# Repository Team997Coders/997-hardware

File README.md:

# 997-Hardware
Repository for FRC 997's custom PCB projects, made in KiCad.

Documentation for each project can be found in their individual directories.

[KiCanvas](https://kicanvas.org/) is recommended for viewing projects from the browser. [Kiri](https://github.com/leoheck/kiri) is a very good tool for visual git diffs of KiCad files, but only runs locally and has quite a few dependencies.

### Installation
This project uses `kicad-cli` and `pcbdraw` in its commit hook script. `kicad-cli` is distributed with the broader KiCad package, and `pcbdraw` can be installed using [these instructions](https://github.com/yaqwsx/PcbDraw/blob/master/doc/installation.md).[^1]

### Licensing
Hardware source files licensed under the GPL v3.0. Some redistributed files may be under different licenses.

[^1]: `pcbdraw` depends on the `mistune` library. `pcbdraw` version 1.1.2 does not depend on the correct version of `mistune` and for some users manually running `pip install mistune==2.0.5` may be required.

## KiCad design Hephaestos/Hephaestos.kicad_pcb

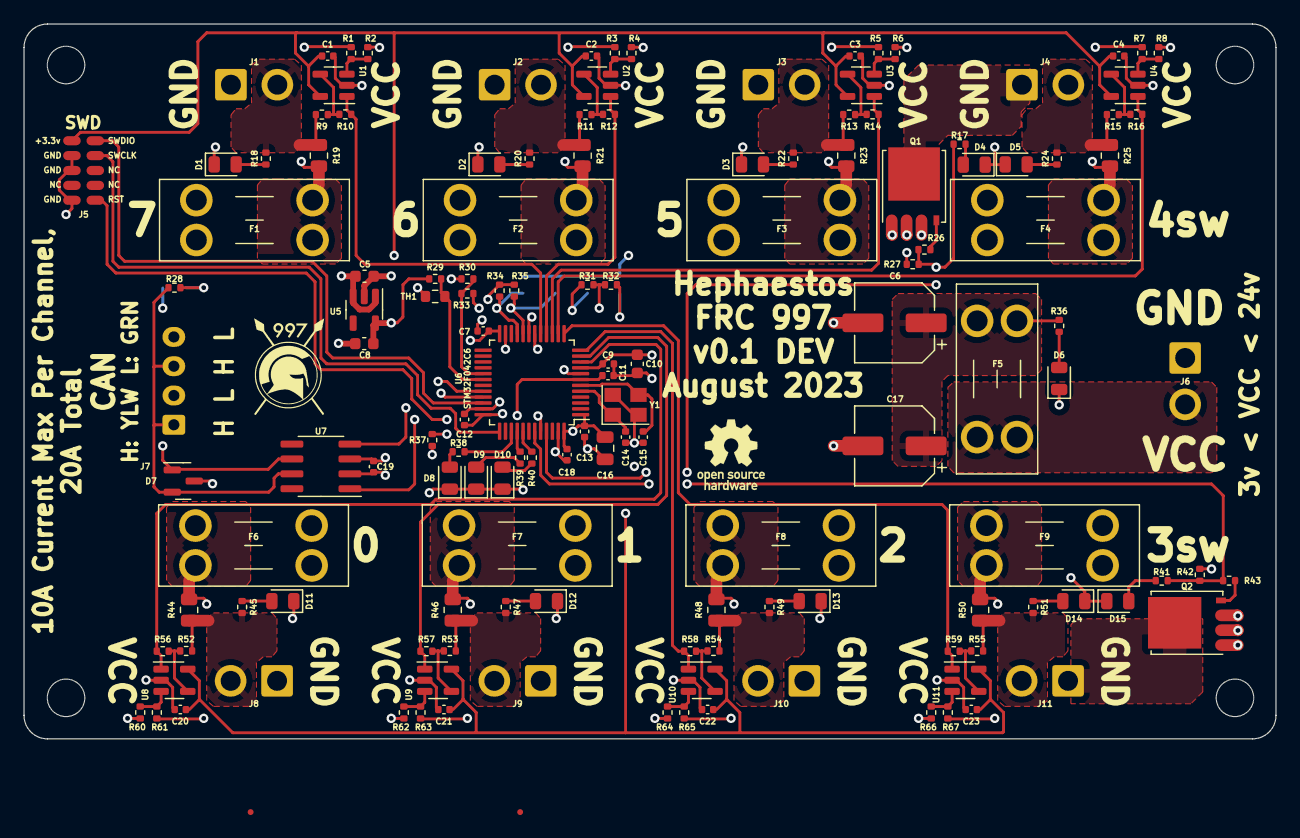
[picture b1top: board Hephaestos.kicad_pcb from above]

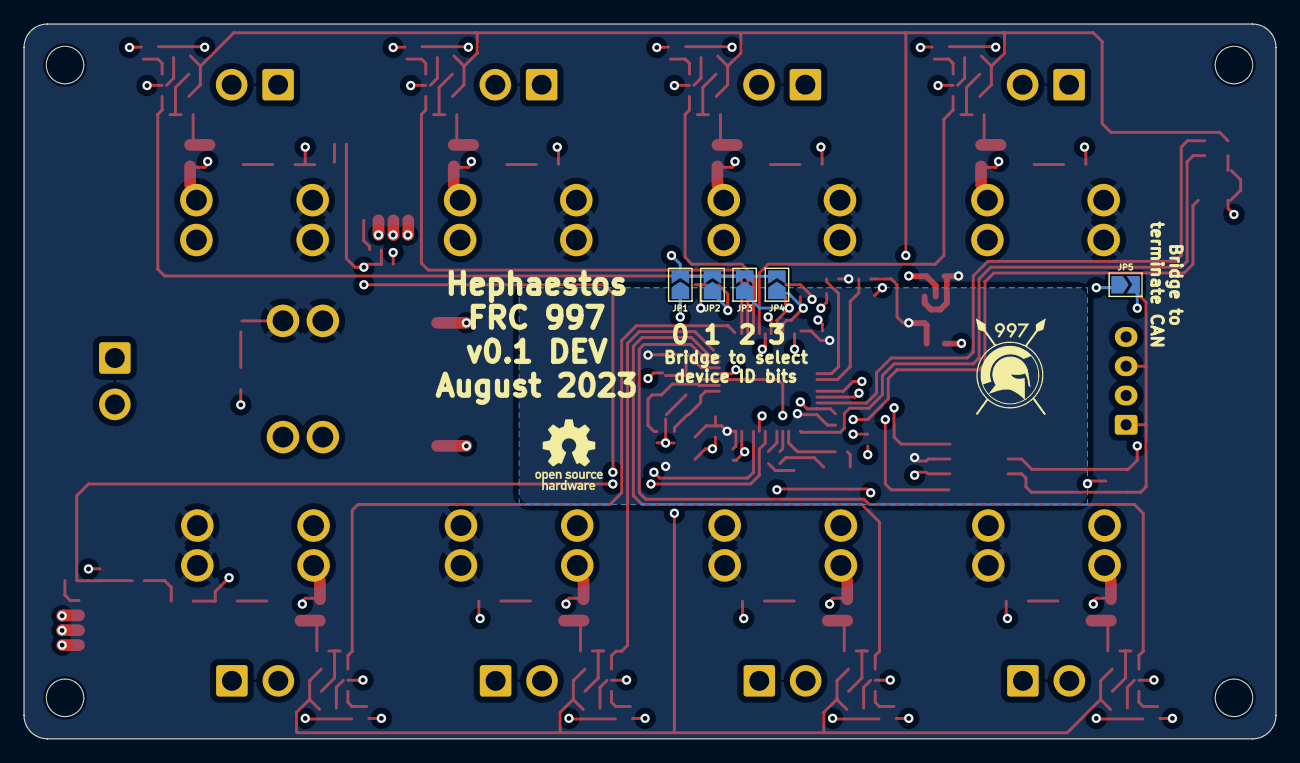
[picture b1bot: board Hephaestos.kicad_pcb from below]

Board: 4 copper layers, 106.8 x 61.0 mm, 149 parts (7 on the bottom side), 84 nets.

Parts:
1, 2: LOGO; 997-big
C1, C2, C3, C4, C7, C9, C11, C12, C13, C18, C19, C20, C21, C22, C23: 0.1 uF; C_0402_1005Metric
C5: 1 uF 35v; C_0603_1608Metric
C6, C17: 100 uF 35v; CP_Elec_6.3x7.7
C8: 2.2 uF; C_0603_1608Metric
C10: 1 uF; C_0603_1608Metric
C14, C15: 10 pF; C_0402_1005Metric
C16: 4.7 uF; C_0805_2012Metric
D1, D2, D3, D5, D6, D8, D11, D12, D13, D14: BLUE; LED_0805_2012Metric
D4, D10, D15: RED; LED_0805_2012Metric
D7: NUP2105L; SOT-23
D9: GREEN; LED_0805_2012Metric
F1, F2, F3, F4, F5, F6, F7, F8, F9: FUSE; Fuseholder_Blade_Mini_Keystone_3568
J1, J2, J3, J4, J6, J8, J9, J10, J11: Conn_01x02; JST_VH_B2P-VH-B_1x02_P3.96mm_Vertical
J5: Conn_02x05_Counter_Clockwise; Tag-Connect_TC2050-IDC-FP_2x05_P1.27mm_Vertical
J7: Conn_01x04; JST_XH_B4B-XH-AM_1x04_P2.50mm_Vertical
JP1, JP2, JP3, JP4, JP5: Jumper_2_Open; SolderJumper-2_P1.3mm_Open_TrianglePad1.0x1.5mm
Q1, Q2: CSD17577Q5A; TDSON-8-1
R1, R3, R5, R7, R9, R11, R13, R15, R17, R41, R52, R53, R54, R55, R61, R63, R65, R67: 200; R_0402_1005Metric
R2, R4, R6, R8, R10, R12, R14, R16, R56, R57, R58, R59, R60, R62, R64, R66: 15k; R_0402_1005Metric
R18, R20, R22, R24, R26, R27, R29, R30, R31, R32, R34, R35, R36, R37, R42, R43, R45, R47, R49, R51: 1k; R_0402_1005Metric
R19, R21, R23, R25, R44, R46, R48, R50: 0.003; R_0805_2012Metric
R28: 120; R_0402_1005Metric
R33, R40: 100; R_0402_1005Metric
R38, R39: 22; R_0402_1005Metric
TH1: thermistor 10k; R_0603_1608Metric
U1, U2, U3, U4, U8, U9, U10, U11: MCP6001-OT; SOT-23-5
U5: AP2205K-3.3; SOT-23-5
U6: STM32F042C6Tx; LQFP-48_7x7mm_P0.5mm
U7: SN65HVD232; SOIC-8_3.9x4.9mm_P1.27mm
Y1: 16 MHz 9 pF; Crystal_SMD_3225-4Pin_3.2x2.5mm
oshw_b: OSHW-Logo_5.7x6mm_SilkScreen
oshw_f: OSHW-Logo_5.7x6mm_SilkScreen

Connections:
+3.3V: C1.1, C2.1, C3.1, C4.1, C7.2, C8.2, C9.2, C10.1, C12.2, C13.2, C16.2, C18.2, C19.2, C20.1, C21.1, C22.1, C23.1, J5.1, R29.1, R31.1, R32.1, R34.1, R35.1, U1.5 (V+), U2.5 (V+), U3.5 (V+), U4.5 (V+), U5.5 (VOUT), U6.1 (VBAT), U6.9 (VDDA), U6.24 (VDD), U6.36 (VDDIO2), U6.48 (VDD), U7.3 (VCC), U8.5 (V+), U9.5 (V+), U10.5 (V+), U11.5 (V+)
/channel0/L: J8.2, R44.1, R45.2, R52.2
/channel1/L: J9.2, R46.1, R47.2, R53.2
/channel2/L: J10.2, R48.1, R49.2, R54.2
/channel3/L: J11.2, R50.1, R51.2, R55.2
/channel4/L: J4.2, R15.2, R24.2, R25.1
/channel5/L: J3.2, R13.2, R22.2, R23.1
/channel6/L: J2.2, R11.2, R20.2, R21.1
/channel7/L: J1.2, R9.2, R18.2, R19.1
A0: R56.2, U6.10 (PA0), U8.1
A1: R57.2, U6.11 (PA1), U9.1
A2: R58.2, U6.12 (PA2), U10.1
A3: R59.2, U6.13 (PA3), U11.1
A4: R16.2, U4.1, U6.14 (PA4)
A5: R14.2, U3.1, U6.15 (PA5)
A6: R12.2, U2.1, U6.16 (PA6)
A7: R10.2, U1.1, U6.17 (PA7)
ADC_THERM: R29.2, TH1.1, U6.30 (PA9)
ADC_VCCDIV: R30.2, R33.1, U6.29 (PA8)
CANH: D7.2 (K), J7.1, J7.3, R28.1, U7.7 (CANH)
CANID_SEL_0: JP1.1 (A), R32.2, U6.18 (PB0)
CANID_SEL_1: JP2.1 (A), R31.2, U6.19 (PB1)
CANID_SEL_2: JP3.1 (A), R35.2, U6.20 (PB2)
CANID_SEL_3: JP4.1 (A), R34.2, U6.21 (PB10)
CANL: D7.1 (K), J7.2, J7.4, JP5.2 (B), U7.6 (CANL)
CAN_RX: U6.32 (PA11), U7.4 (R)
CAN_TX: U6.33 (PA12), U7.1 (D)
CLK_A: C14.2, U6.5 (PF0), Y1.1
CLK_B: C15.1, U6.6 (PF1), Y1.3
GND: C1.2, C2.2, C3.2, C4.2, C5.2, C6.2, C7.1, C8.1, C9.1, C10.2, C11.1, C12.1, C13.1, C14.1, C15.2, C16.1, C17.2, C18.1, C19.1, C20.2, C21.2, C22.2, C23.2, D1.1 (K), D2.1 (K), D3.1 (K), D4.1 (K), D5.1 (K), D6.1 (K), D7.3 (A), D8.1 (K), D9.1 (K), D10.1 (K), D11.1 (K), D12.1 (K), D13.1 (K), D14.1 (K), D15.1 (K), J1.1, J2.1, J3.1, J5.2, J5.3, J5.5, J6.1, J8.1, J9.1, J10.1, JP1.2 (B), JP2.2 (B), JP3.2 (B), JP4.2 (B), Q1.1 (S), Q1.2 (S), Q1.3 (S), Q2.1 (S), Q2.2 (S), Q2.3 (S), R2.2, R4.2, R6.2, R8.2, R27.2, R33.2, R37.2, R42.2, R60.2, R62.2, R64.2, R66.2, TH1.2, U1.2 (V-), U2.2 (V-), U3.2 (V-), U4.2 (V-), U5.2 (GND), U6.8 (VSSA), U6.23 (VSS), U6.35 (VSS), U6.47 (VSS), U7.2 (GND), U8.2 (V-), U9.2 (V-), U10.2 (V-), U11.2 (V-), Y1.2, Y1.4
LED_B: R38.1, U6.39 (PB3)
LED_G: R39.1, U6.40 (PB4)
LED_R: R40.1, U6.41 (PB5)
unnamed: D1.2 (A), R18.1
unnamed: D2.2 (A), R20.1
unnamed: D3.2 (A), R22.1
unnamed: D4.2 (A), R17.1
unnamed: D5.2 (A), R24.1
unnamed: D6.2 (A), R36.1
unnamed: D8.2 (A), R38.2
unnamed: D9.2 (A), R39.2
unnamed: D10.2 (A), R40.2
unnamed: D11.2 (A), R45.1
unnamed: D12.2 (A), R47.1
unnamed: D13.2 (A), R49.1
unnamed: D14.2 (A), R51.1
unnamed: D15.2 (A), R41.1
unnamed: F1.1, R1.2, R19.2
unnamed: F2.1, R3.2, R21.2
unnamed: F3.1, R5.2, R23.2
unnamed: F4.1, R7.2, R25.2
unnamed: F6.1, R44.2, R61.2
unnamed: F7.1, R46.2, R63.2
unnamed: F8.1, R48.2, R65.2
unnamed: F9.1, R50.2, R67.2
unnamed: J4.1, Q1.5 (D)
unnamed: F5.1, J6.2
unnamed: J11.1, Q2.5 (D)
unnamed: JP5.1 (A), R28.2
unnamed: Q1.4 (G), R26.2
unnamed: Q2.4 (G), R43.2
unnamed: R1.1, R2.1, U1.3 (+)
unnamed: R9.1, R10.1, U1.4 (-)
unnamed: R3.1, R4.1, U2.3 (+)
unnamed: R11.1, R12.1, U2.4 (-)
unnamed: R5.1, R6.1, U3.3 (+)
unnamed: R13.1, R14.1, U3.4 (-)
unnamed: R7.1, R8.1, U4.3 (+)
unnamed: R15.1, R16.1, U4.4 (-)
unnamed: R60.1, R61.1, U8.3 (+)
unnamed: R52.1, R56.1, U8.4 (-)
unnamed: R62.1, R63.1, U9.3 (+)
unnamed: R53.1, R57.1, U9.4 (-)
unnamed: R64.1, R65.1, U10.3 (+)
unnamed: R54.1, R58.1, U10.4 (-)
unnamed: R66.1, R67.1, U11.3 (+)
unnamed: R55.1, R59.1, U11.4 (-)
unnamed: R37.1, U6.44 (PF11)
RST: C11.2, J5.6, U6.7 (NRST)
SW3: R41.2, R42.1, R43.1, U6.43 (PB7)
SW4: R17.2, R26.1, R27.1, U6.45 (PB8)
SWCLK: J5.9, U6.37 (PA14)
SWDIO: J5.10, U6.34 (PA13)
VCC: C5.1, C6.1, C17.1, F1.2, F2.2, F3.2, F4.2, F5.2, F6.2, F7.2, F8.2, F9.2, R30.1, R36.2, U5.1 (VIN), U5.3 (EN)

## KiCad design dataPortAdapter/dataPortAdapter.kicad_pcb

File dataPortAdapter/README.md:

# Data Port Adapter

<center> </center>

A simple, completely passive board to convert between the slightly different pinouts of the SparkMAX and the SRX Mag Encoder, intended as a way to get a simpler and cheaper absolute encoder option mechanically compatible with the de-facto standard CANCoder.

The STEP file REV-11-2158 (for 3d visualization) is redistributed from REV Robotics and subject to its original licensing.

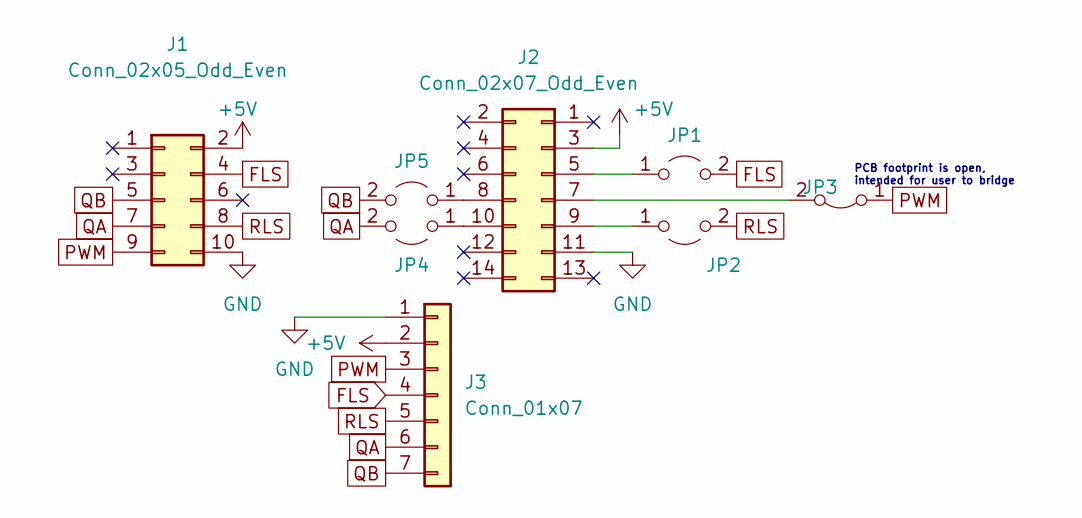
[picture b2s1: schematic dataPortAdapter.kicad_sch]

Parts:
J1: Conn_02x05_Odd_Even; PinHeader_2x05_P1.27mm_Vertical
J2: Conn_02x07_Odd_Even; PinHeader_2x07_P1.27mm_Vertical
J3: Conn_01x07; PinSocket_1x07_P2.54mm_Vertical
JP1, JP2, JP4, JP5: Jumper_2_Open; SolderJumper-2_P1.3mm_Open_TrianglePad1.0x1.5mm
JP3: Jumper_2_Bridged; SolderJumper-2_P1.3mm_Open_TrianglePad1.0x1.5mm

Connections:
+5V: J1.2, J2.3, J3.2
FLS: J1.4, J3.4, JP1.2 (B)
GND: J1.10, J2.11, J3.1
unnamed: J2.5, JP1.1 (A)
unnamed: J2.7, JP3.2 (B)
unnamed: J2.8, JP5.1 (A)
unnamed: J2.9, JP2.1 (A)
unnamed: J2.10, JP4.1 (A)
PWM: J1.9, J3.3, JP3.1 (A)
QA: J1.7, J3.6, JP4.2 (B)
QB: J1.5, J3.7, JP5.2 (B)
RLS: J1.8, J3.5, JP2.2 (B)

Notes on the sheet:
PCB footprint is open, intended for user to bridge

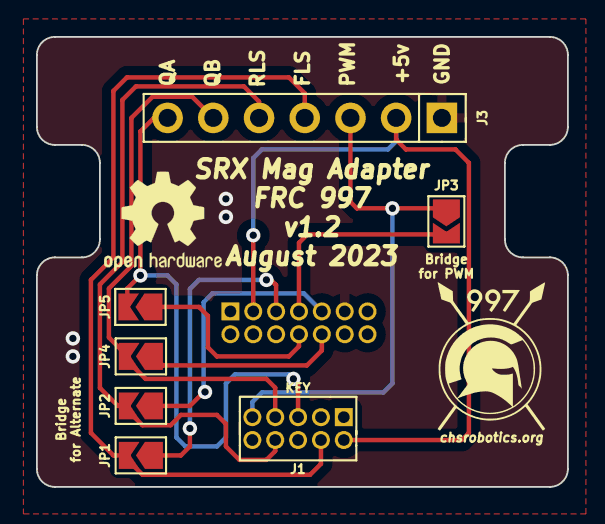
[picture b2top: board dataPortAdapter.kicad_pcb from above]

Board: 2 copper layers, 29.5 x 25.0 mm, 8 parts (1 on the bottom side), 12 nets.

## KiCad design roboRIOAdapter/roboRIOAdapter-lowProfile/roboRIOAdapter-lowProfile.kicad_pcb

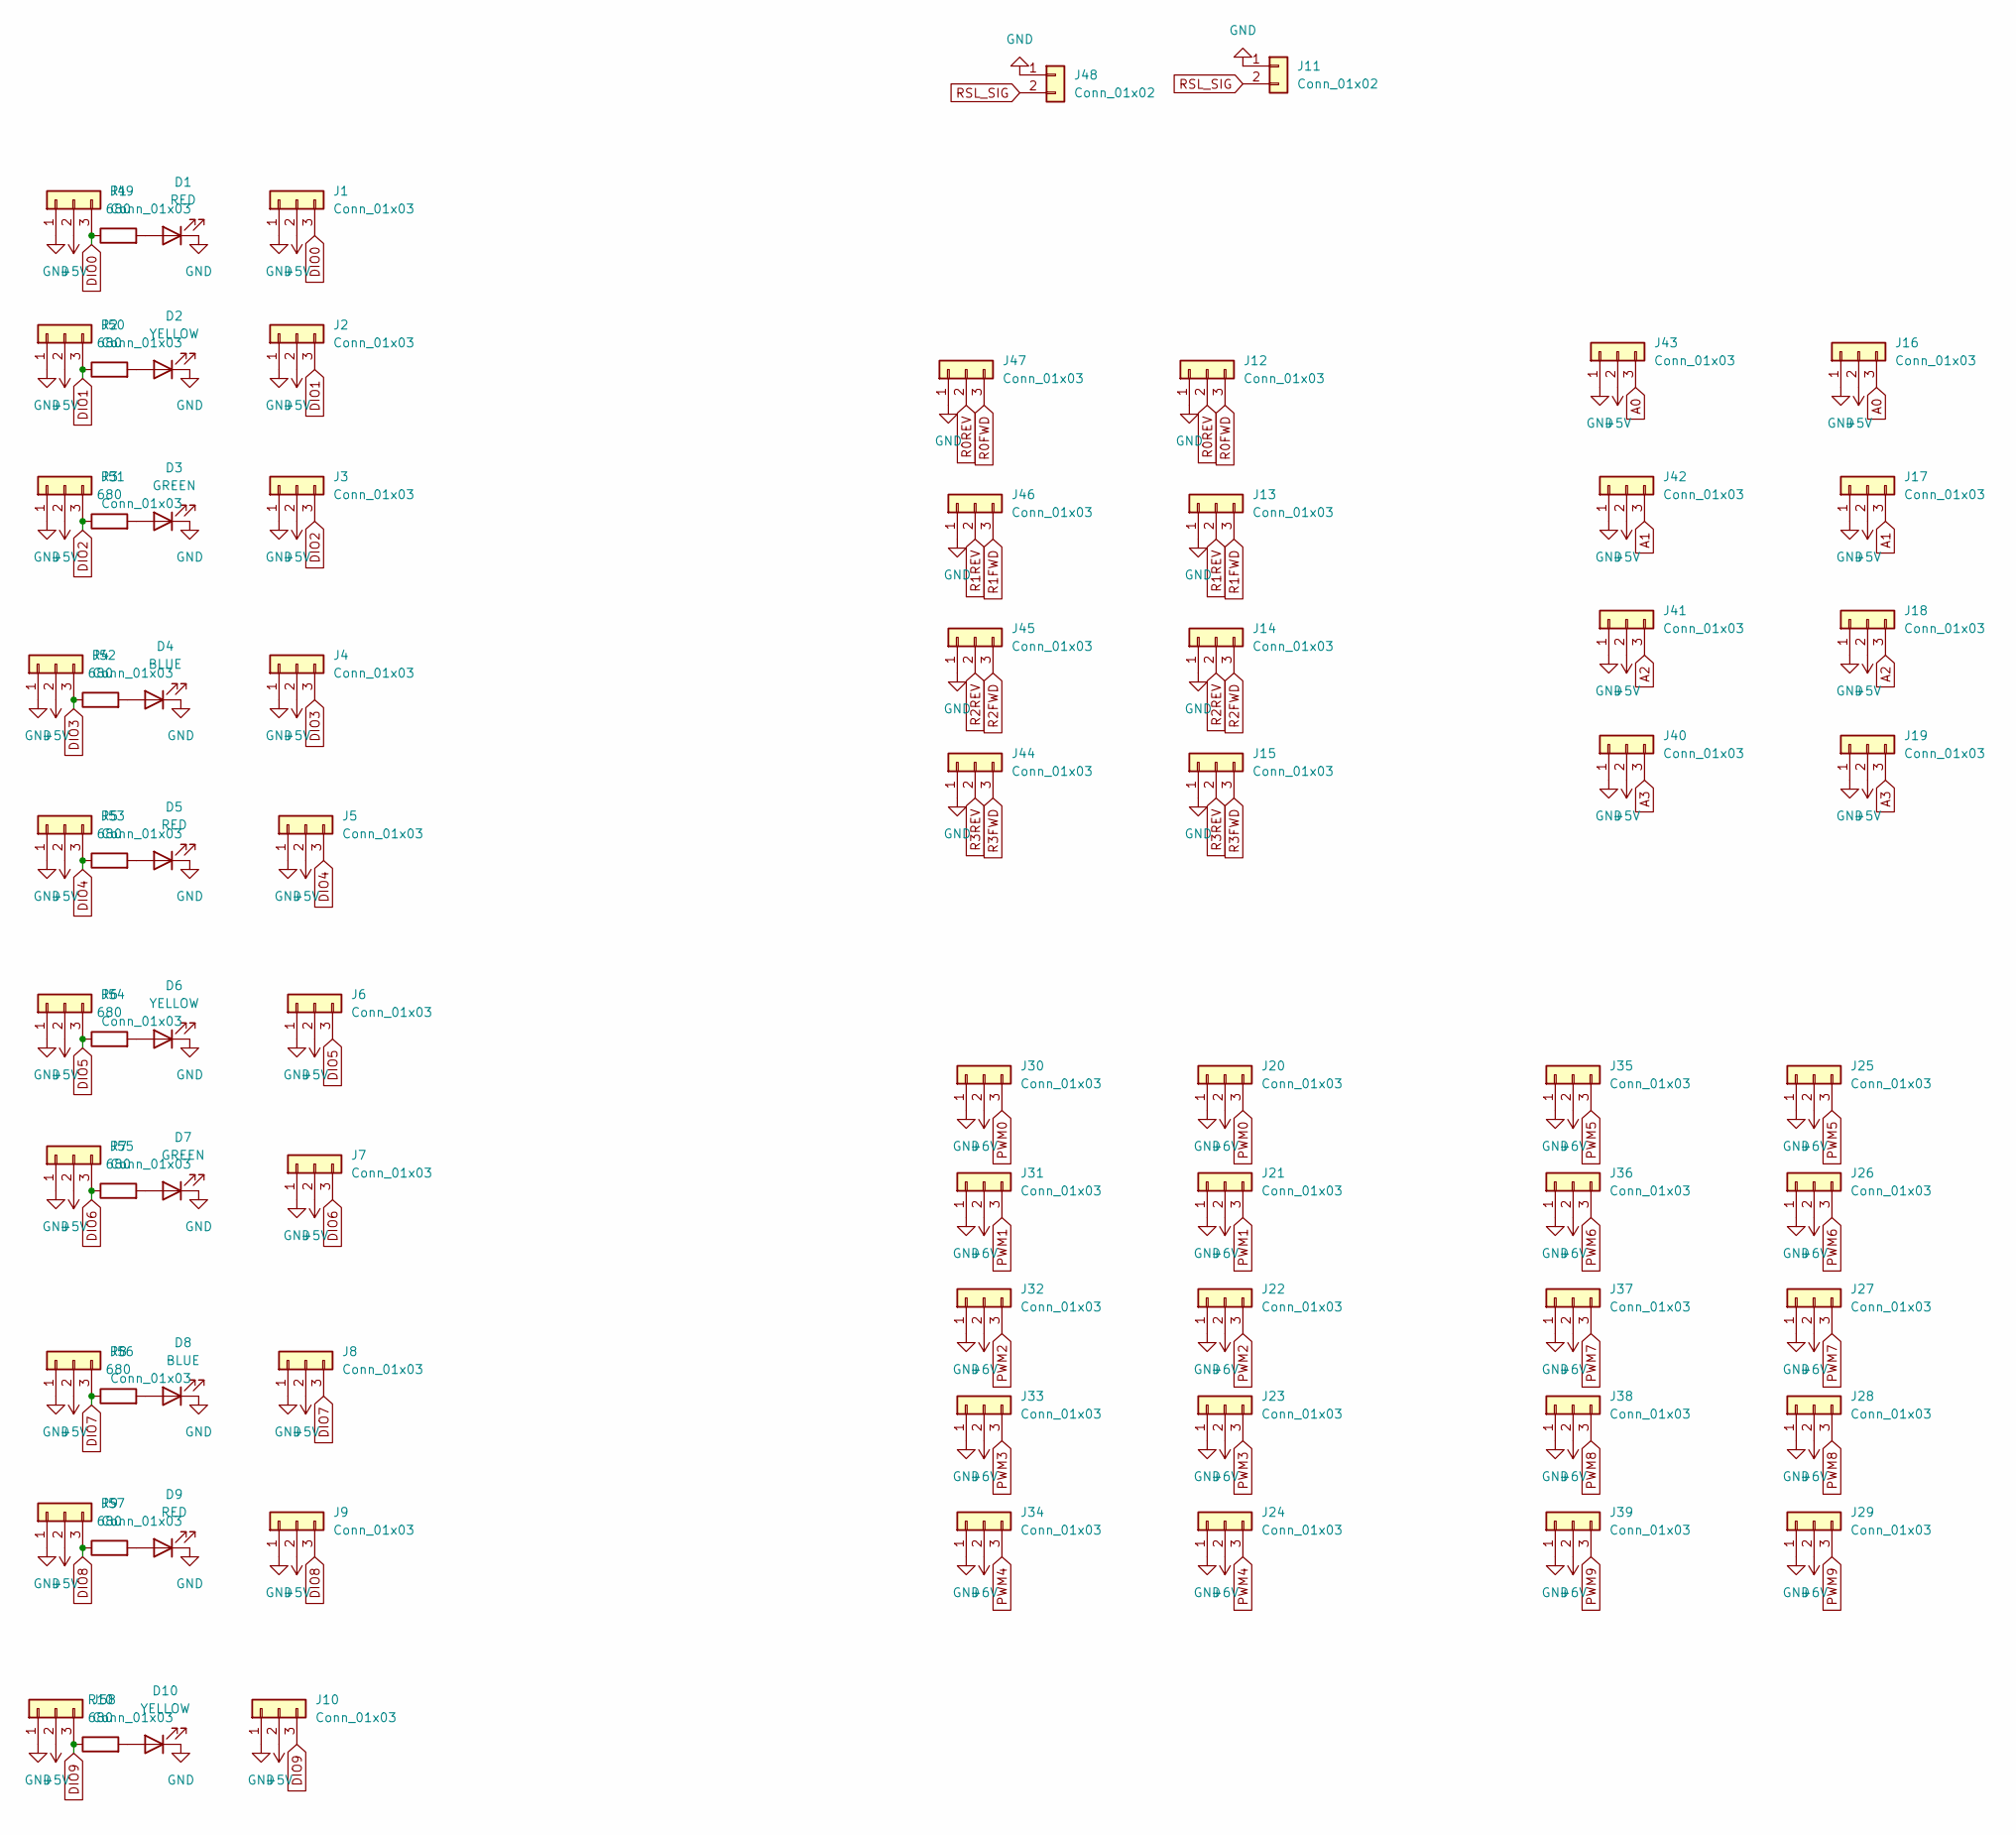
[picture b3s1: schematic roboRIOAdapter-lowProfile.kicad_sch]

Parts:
D1, D5, D9: RED; LED_0603_1608Metric
D2, D6, D10: YELLOW; LED_0603_1608Metric
D3, D7: GREEN; LED_0603_1608Metric
D4, D8: BLUE; LED_0603_1608Metric
J1, J2, J3, J4, J5, J6, J7, J8, J9, J10, J12, J13, J14, J15, J16, J17, J18, J19, J20, J21, J22, J23, J24, J25, J26, J27, J28, J29: Conn_01x03; JST_XH_B3B-XH-A_1x03_P2.50mm_Vertical
J11: Conn_01x02; JST_XH_B2B-XH-A_1x02_P2.50mm_Vertical
J30, J31, J32, J33, J34, J35, J36, J37, J38, J39, J40, J41, J42, J43, J44, J45, J46, J47, J49, J50, J51, J52, J53, J54, J55, J56, J57, J58: Conn_01x03; PinSocket_1x03_P2.54mm_Vertical
J48: Conn_01x02; PinSocket_1x02_P2.54mm_Vertical
R1, R2, R3, R4, R5, R6, R7, R8, R9, R10: 680; R_0603_1608Metric

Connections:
+5V: J1.2, J2.2, J3.2, J4.2, J5.2, J6.2, J7.2, J8.2, J9.2, J10.2, J16.2, J17.2, J18.2, J19.2, J40.2, J41.2, J42.2, J43.2, J49.2, J50.2, J51.2, J52.2, J53.2, J54.2, J55.2, J56.2, J57.2, J58.2
+6V: J20.2, J21.2, J22.2, J23.2, J24.2, J25.2, J26.2, J27.2, J28.2, J29.2, J30.2, J31.2, J32.2, J33.2, J34.2, J35.2, J36.2, J37.2, J38.2, J39.2
A0: J16.3, J43.3
A1: J17.3, J42.3
A2: J18.3, J41.3
A3: J19.3, J40.3
DIO0: J1.3, J49.3, R1.1
DIO1: J2.3, J50.3, R2.1
DIO2: J3.3, J51.3, R3.1
DIO3: J4.3, J52.3, R4.1
DIO4: J5.3, J53.3, R5.1
DIO5: J6.3, J54.3, R6.1
DIO6: J7.3, J55.3, R7.1
DIO7: J8.3, J56.3, R8.1
DIO8: J9.3, J57.3, R9.1
DIO9: J10.3, J58.3, R10.1
GND: D1.1 (K), D2.1 (K), D3.1 (K), D4.1 (K), D5.1 (K), D6.1 (K), D7.1 (K), D8.1 (K), D9.1 (K), D10.1 (K), J1.1, J2.1, J3.1, J4.1, J5.1, J6.1, J7.1, J8.1, J9.1, J10.1, J11.1, J12.1, J13.1, J14.1, J15.1, J16.1, J17.1, J18.1, J19.1, J20.1, J21.1, J22.1, J23.1, J24.1, J25.1, J26.1, J27.1, J28.1, J29.1, J30.1, J31.1, J32.1, J33.1, J34.1, J35.1, J36.1, J37.1, J38.1, J39.1, J40.1, J41.1, J42.1, J43.1, J44.1, J45.1, J46.1, J47.1, J48.1, J49.1, J50.1, J51.1, J52.1, J53.1, J54.1, J55.1, J56.1, J57.1, J58.1
unnamed: D1.2 (A), R1.2
unnamed: D2.2 (A), R2.2
unnamed: D3.2 (A), R3.2
unnamed: D4.2 (A), R4.2
unnamed: D5.2 (A), R5.2
unnamed: D6.2 (A), R6.2
unnamed: D7.2 (A), R7.2
unnamed: D8.2 (A), R8.2
unnamed: D9.2 (A), R9.2
unnamed: D10.2 (A), R10.2
PWM0: J20.3, J30.3
PWM1: J21.3, J31.3
PWM2: J22.3, J32.3
PWM3: J23.3, J33.3
PWM4: J24.3, J34.3
PWM5: J25.3, J35.3
PWM6: J26.3, J36.3
PWM7: J27.3, J37.3
PWM8: J28.3, J38.3
PWM9: J29.3, J39.3
R0FWD: J12.3, J47.3
R0REV: J12.2, J47.2
R1FWD: J13.3, J46.3
R1REV: J13.2, J46.2
R2FWD: J14.3, J45.3
R2REV: J14.2, J45.2
R3FWD: J15.3, J44.3
R3REV: J15.2, J44.2
RSL_SIG: J11.2, J48.2

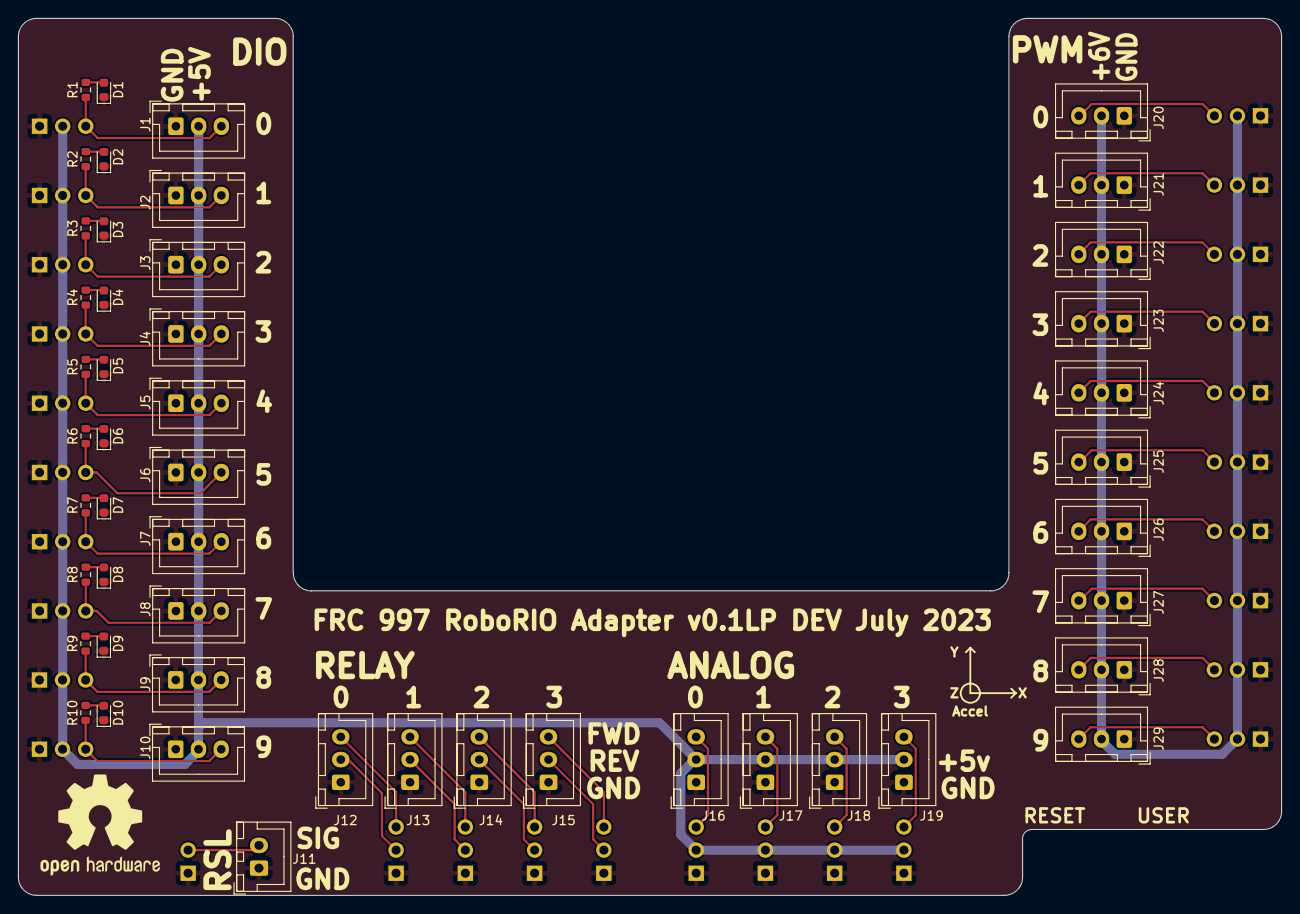
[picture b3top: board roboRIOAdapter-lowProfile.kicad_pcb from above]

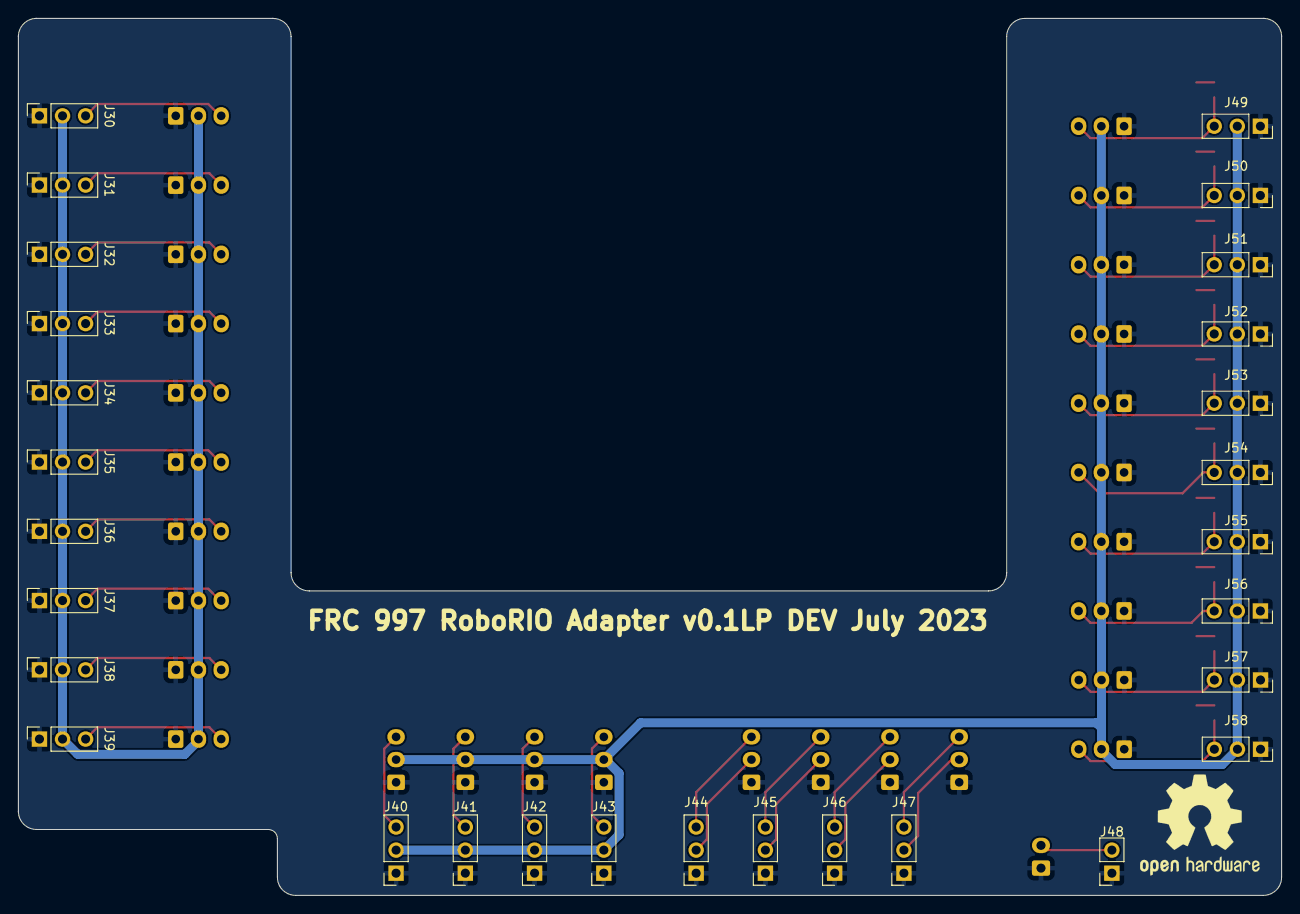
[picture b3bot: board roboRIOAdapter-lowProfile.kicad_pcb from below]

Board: 4 copper layers, 139.0 x 96.5 mm, 78 parts (29 on the bottom side), 46 nets.

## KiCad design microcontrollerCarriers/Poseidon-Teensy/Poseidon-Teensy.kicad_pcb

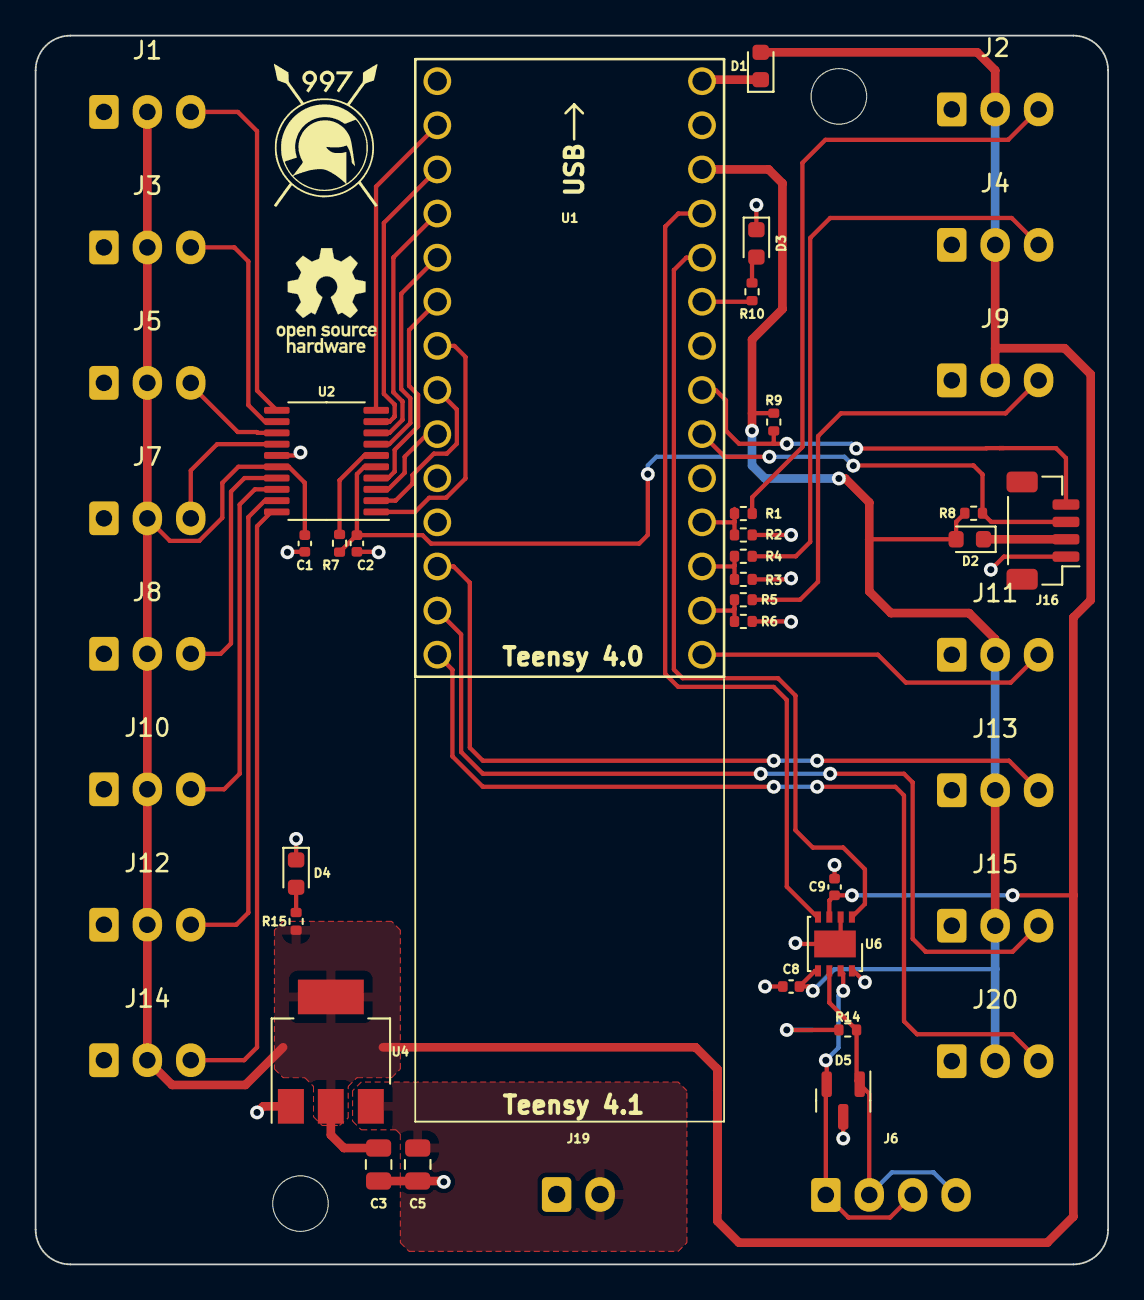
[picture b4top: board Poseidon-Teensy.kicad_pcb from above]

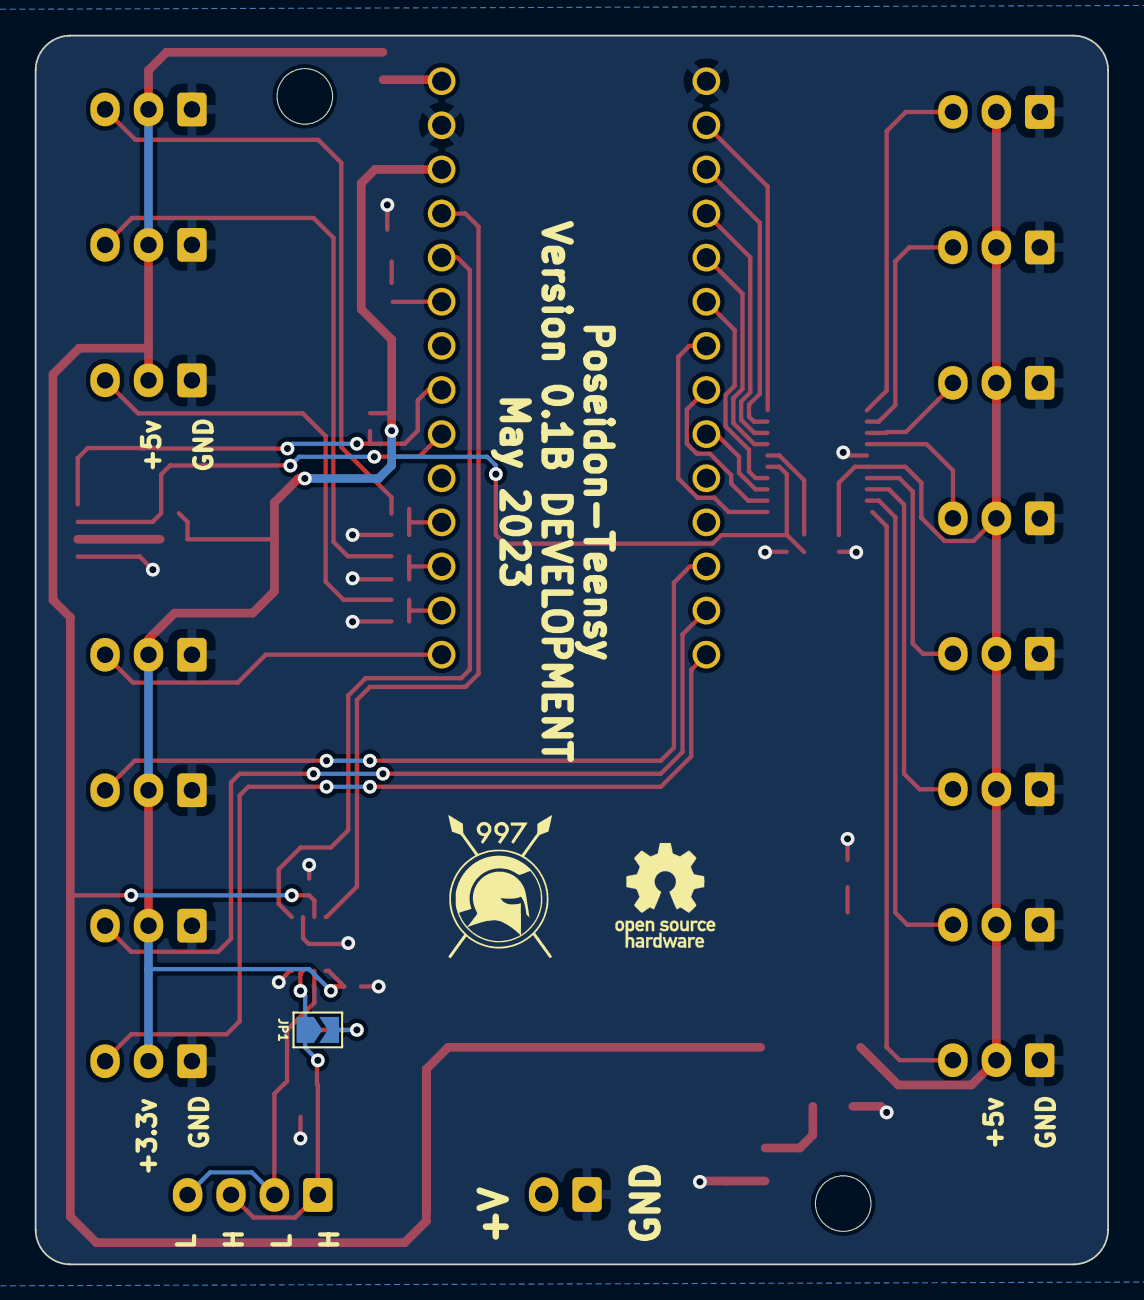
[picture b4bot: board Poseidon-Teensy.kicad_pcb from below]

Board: 4 copper layers, 61.8 x 70.8 mm, 50 parts (3 on the bottom side), 43 nets.

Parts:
1, 2: LOGO; 997-big
C1, C2, C8, C9: 0.1 uF; C_0402_1005Metric
C3, C5: 10 uF; C_0805_2012Metric
D1, D2: D_Schottky; D_0603_1608Metric
D3, D4: LED; LED_0603_1608Metric
D5: NUP2105L; SOT-23
J1, J2, J3, J4, J5, J7, J8, J9, J10, J11, J12, J13, J14, J15, J20: Conn_01x03; JST_XH_B3B-XH-A_1x03_P2.50mm_Vertical
J6: Conn_01x04; JST_XH_B4B-XH-A_1x04_P2.50mm_Vertical
J16: Conn_01x04; JST_SH_BM04B-SRSS-TB_1x04-1MP_P1.00mm_Vertical
J19: Conn_01x02; JST_XH_B2B-XH-A_1x02_P2.50mm_Vertical
JP1: Jumper_2_Open; SolderJumper-2_P1.3mm_Open_TrianglePad1.0x1.5mm
R1, R4, R5: 1.5k; R_0402_1005Metric
R2, R3, R6: 2.7k; R_0402_1005Metric
R7, R8, R9: 10k; R_0402_1005Metric
R10, R15: 300; R_0402_1005Metric
R14: 120; R_0402_1005Metric
U1: Teensy4.0; Teensy40
U2: TXB0108DQSR; TSSOP-20_4.4x6.5mm_P0.65mm
U4: NCP1117-5.0_SOT223; SOT-223-3_TabPin2
U6: MCP2542FDxMF; DFN-8-1EP_3x3mm_P0.65mm_EP1.55x2.4mm
oshw_b: OSHW-Logo_5.7x6mm_SilkScreen
oshw_f: OSHW-Logo_5.7x6mm_SilkScreen

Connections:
3ADC0: R5.2, R6.1, U1.21 (14_A0_TX3_SPDIF_OUT)
3ADC1: R3.1, R4.2, U1.22 (15_A1_RX3_SPDIF_IN)
3ADC2: R1.2, R2.1, U1.23 (16_A2_RX4_SCL1)
3GPIO0: U1.2 (0_RX1_CRX2_CS1), U2.10 (A8)
3GPIO1: U1.3 (1_TX1_CTX2_MISO1), U2.9 (A7)
3GPIO2: U1.4 (2_OUT2), U2.8 (A6)
3GPIO3: U1.5 (3_LRCLK2), U2.7 (A5)
3GPIO4: U1.6 (4_BCLK2), U2.4 (A4)
3GPIO5: U1.9 (7_RX2_OUT1A), U2.3 (A3)
3GPIO6: U1.8 (6_OUT1D), U2.2 (A2)
3GPIO7: U1.7 (5_IN2), U2.1 (A1)
3GPIO8: J20.3, U1.14 (12_MISO_MQSL)
3GPIO9: J15.3, U1.13 (11_MOSI_CTX1)
3GPIO10: J13.3, U1.12 (10_CS_MQSR)
3GPIO11: J11.3, U1.20 (13_SCK_CRX1_LED)
5ADC0: J9.3, R5.1
5ADC1: J4.3, R4.1
5ADC2: J2.3, R1.1
5GPIO0: J1.3, U2.11 (B8)
5GPIO1: J3.3, U2.12 (B7)
5GPIO2: J5.3, U2.13 (B6)
5GPIO3: J7.3, U2.14 (B5)
5GPIO4: J8.3, U2.17 (B4)
5GPIO5: J10.3, U2.18 (B3)
5GPIO6: J12.3, U2.19 (B2)
5GPIO7: J14.3, U2.20 (B1)
+3.3V: C2.1, C8.1, D2.2 (A), J11.2, J13.2, J15.2, J20.2, R7.1, R8.1, R9.1, U1.31 (3V3), U2.5 (VCCA), U6.5 (VIO)
+5V: C1.1, C3.1, C9.2, D1.2 (A), J1.2, J2.2, J3.2, J4.2, J5.2, J7.2, J8.2, J9.2, J10.2, J12.2, J14.2, R15.2, U2.16 (VCCB), U4.2 (VO), U6.3 (VDD)
CANH: D5.2 (K), J6.1, J6.3, JP1.1 (A), U6.7 (CANH)
CANL: D5.1 (K), J6.2, J6.4, R14.2, U6.6 (CANL)
GND: C1.2, C2.2, C3.2, C5.2, C8.2, C9.1, D3.1 (K), D4.1 (K), D5.3 (A), J1.1, J2.1, J3.1, J4.1, J5.1, J7.1, J8.1, J9.1, J10.1, J11.1, J12.1, J13.1, J14.1, J15.1, J16.1, J19.1, J20.1, R2.2, R3.2, R6.2, U1.1 (GND), U1.32 (GND), U2.15 (GND), U4.1 (GND), U6.2 (VSS), U6.8 (STBY), U6.9 (VSS)
unnamed: D1.1 (K), U1.33 (VIN)
unnamed: D2.1 (K), J16.2
unnamed: D3.2 (A), R10.1
unnamed: D4.2 (A), R15.1
unnamed: JP1.2 (B), R14.1
unnamed: R10.2, U1.28 (21_A7_RX5_BCLK1)
unnamed: R7.2, U2.6 (OE)
RXCAN: U1.30 (23_A9_CRX1_MCLK1), U6.4 (RXD)
SCL: J16.4, R9.2, U1.26 (19_A5_SCL0)
SDA: J16.3, R8.2, U1.25 (18_A4_SDA0)
TXCAN: U1.29 (22_A8_CTX1), U6.1 (TXD)
VIN: C5.1, J19.2, U4.3 (VI)
